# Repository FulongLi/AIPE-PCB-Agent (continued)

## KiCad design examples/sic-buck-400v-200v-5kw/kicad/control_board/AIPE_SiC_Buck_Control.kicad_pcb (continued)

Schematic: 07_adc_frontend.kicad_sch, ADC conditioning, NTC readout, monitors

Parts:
C63, C64: 1u/50V; C_0805_2012Metric
C65, C66, C67: 100n/50V; C_0603_1608Metric
C68, C69, C70, C71, C72, C73, C74, C75: 1n/50V; C_0603_1608Metric
J7: J_NTC: Vishay NTCALUG01A103F heatsink lug NTC (10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; PinHeader_1x02_P2.54mm_Vertical
R64: 2.2k; R_0603_1608Metric
R65: 32.4k; R_0603_1608Metric
R66: 10k; R_0603_1608Metric
R67, R68, R69, R70, R71, R72, R73, R74: 1k; R_0603_1608Metric
U15: REF3130AIDBZR; SOT-23
U16: LM61CIM3/NOPB; SOT-23

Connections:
3V3: C63.1, C67.1, U15.1 (IN), U16.1 (+VS); also elsewhere on the board
ADC_I12V: C73.1, R72.2; also elsewhere on the board
ADC_ISENSE: C69.1, R68.2; also elsewhere on the board
ADC_ISENSE_REF: C72.1, R71.2; also elsewhere on the board
ADC_TEMP_CTRL: C71.1, R70.2; also elsewhere on the board
ADC_TEMP_HS: C70.1, R69.2; also elsewhere on the board
ADC_V12V: C75.1, R74.2; also elsewhere on the board
ADC_VIN: C68.1, R67.2; also elsewhere on the board
ADC_VOUT: C74.1, R73.2; also elsewhere on the board
GND_CTRL: C63.2, C64.2, C65.2, C66.2, C67.2, C68.2, C69.2, C70.2, C71.2, C72.2, C73.2, C74.2, C75.2, J7.2, R66.2, U15.3 (GND), U16.3 (GND); also elsewhere on the board
I12V_MON: R72.1; also elsewhere on the board
ISENSE: R68.1; also elsewhere on the board
ISENSE_REF: R71.1; also elsewhere on the board
OTP_REF: C66.1, R65.2, R66.1; also elsewhere on the board
REF3V0: C64.1, R64.1, R65.1, U15.2 (OUT)
TEMP_CTRL: R70.1, U16.2 (VOUT)
TEMP_HS_NTC: C65.1, J7.1, R64.2, R69.1; also elsewhere on the board
V12V_MON: R74.1; also elsewhere on the board
VIN_SENSE: R67.1; also elsewhere on the board
VOUT_SENSE: R73.1; also elsewhere on the board

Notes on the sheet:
ADC conditioning, NTC readout, monitors
1 k + 1 nF at every ADC input; heatsink NTC with 2.2 k to REF3V0 (REF3130); OTP threshold 42.2 k / 10 k = 0.575 V (110 C); LM61.
REF3130, heatsink NTC, OTP threshold, LM61
ADC anti-alias RC networks

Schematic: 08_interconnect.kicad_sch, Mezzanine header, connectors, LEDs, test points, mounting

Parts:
D3, D6: LED red; LED_0805_2012Metric
D4, D5: LED green; LED_0805_2012Metric
H1, H2, H3, H4: M3; MountingHole_3.2mm_M3
J8: J_MEZZ: 2 x 25 header to the power-board SSW-125-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; PinHeader_2x25_P2.54mm_Vertical
R75: 10k; R_0603_1608Metric
R76: 4.7k; R_0603_1608Metric
R77, R78, R79: 1.5k; R_0603_1608Metric
TP1: 3V3; TestPoint_Pad_D2.0mm
TP2: 1V9; TestPoint_Pad_D2.0mm
TP3: 5V; TestPoint_Pad_D2.0mm
TP4: 12V_PROT; TestPoint_Pad_D2.0mm
TP5, TP6: GND_CTRL; TestPoint_Pad_D2.0mm
TP7: PWM_H; TestPoint_Pad_D2.0mm
TP8: PWM_L; TestPoint_Pad_D2.0mm
TP9: FAULT_N; TestPoint_Pad_D2.0mm
TP10: ARM; TestPoint_Pad_D2.0mm
TP11: FAULT_LATCH_N; TestPoint_Pad_D2.0mm
TP12: GATE_EN; TestPoint_Pad_D2.0mm
TP13: XRS_N; TestPoint_Pad_D2.0mm
TP14: VIN_SENSE; TestPoint_Pad_D2.0mm
TP15: VOUT_SENSE; TestPoint_Pad_D2.0mm
TP16: ISENSE; TestPoint_Pad_D2.0mm

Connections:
1V9: TP2.1; also elsewhere on the board
3V3: J8.39, J8.40, R75.1, TP1.1; also elsewhere on the board
5V: TP3.1; also elsewhere on the board
12V_PROT: J8.1, J8.2, J8.3, R76.1, TP4.1; also elsewhere on the board
ARM: TP10.1; also elsewhere on the board
BIAS_EN: J8.9; also elsewhere on the board
FAN_TACH: J8.29, R75.2; also elsewhere on the board
FAULT_LATCH_N: TP11.1; also elsewhere on the board
FAULT_N: J8.35, R77.1, TP9.1; also elsewhere on the board
FLT_H_N: J8.20; also elsewhere on the board
FLT_L_N: J8.21; also elsewhere on the board
GATE_EN: TP12.1; also elsewhere on the board
GND_CTRL: D3.1 (K), D4.1 (K), D5.1 (K), D6.1 (K), J8.4, J8.5, J8.6, J8.8, J8.10, J8.12, J8.13, J8.15, J8.16, J8.18, J8.19, J8.22, J8.25, J8.26, J8.28, J8.31, J8.34, J8.38, J8.41, J8.42, J8.44, J8.46, J8.48, J8.50, TP5.1, TP6.1; also elsewhere on the board
ISENSE: J8.43, TP16.1; also elsewhere on the board
ISENSE_REF: J8.45; also elsewhere on the board
LED_12V_A: D3.2 (A), R76.2
LED_ARMED_A: D4.2 (A), R77.2
LED_FAULT: R79.1; also elsewhere on the board
LED_FAULT_A: D6.2 (A), R79.2
LED_RUN: R78.1; also elsewhere on the board
LED_RUN_A: D5.2 (A), R78.2
OC_N: J8.27; also elsewhere on the board
PG_BIAS_H_N: J8.32; also elsewhere on the board
PG_BIAS_L_N: J8.33; also elsewhere on the board
PG_BIAS_S_N: J8.30; also elsewhere on the board
PWM_H: J8.14, TP7.1; also elsewhere on the board
PWM_L: J8.17, TP8.1; also elsewhere on the board
RDY_H: J8.23; also elsewhere on the board
RDY_L: J8.24; also elsewhere on the board
RELAY_ON: J8.7; also elsewhere on the board
RESET_N: J8.11; also elsewhere on the board
SPARE_D1: J8.36; also elsewhere on the board
SPARE_D2: J8.37; also elsewhere on the board
VIN_SENSE: J8.47, TP14.1; also elsewhere on the board
VOUT_SENSE: J8.49, TP15.1; also elsewhere on the board
XRS_N: TP13.1; also elsewhere on the board

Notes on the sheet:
Mezzanine header, connectors, LEDs, test points, mounting
Mezzanine header TSW-125-07-G-D (pin assignment per design_decisions.json), indicator LEDs, test pads, 4 x M3.
Mezzanine header to the power board
Indicator LEDs
Test points
Mechanical

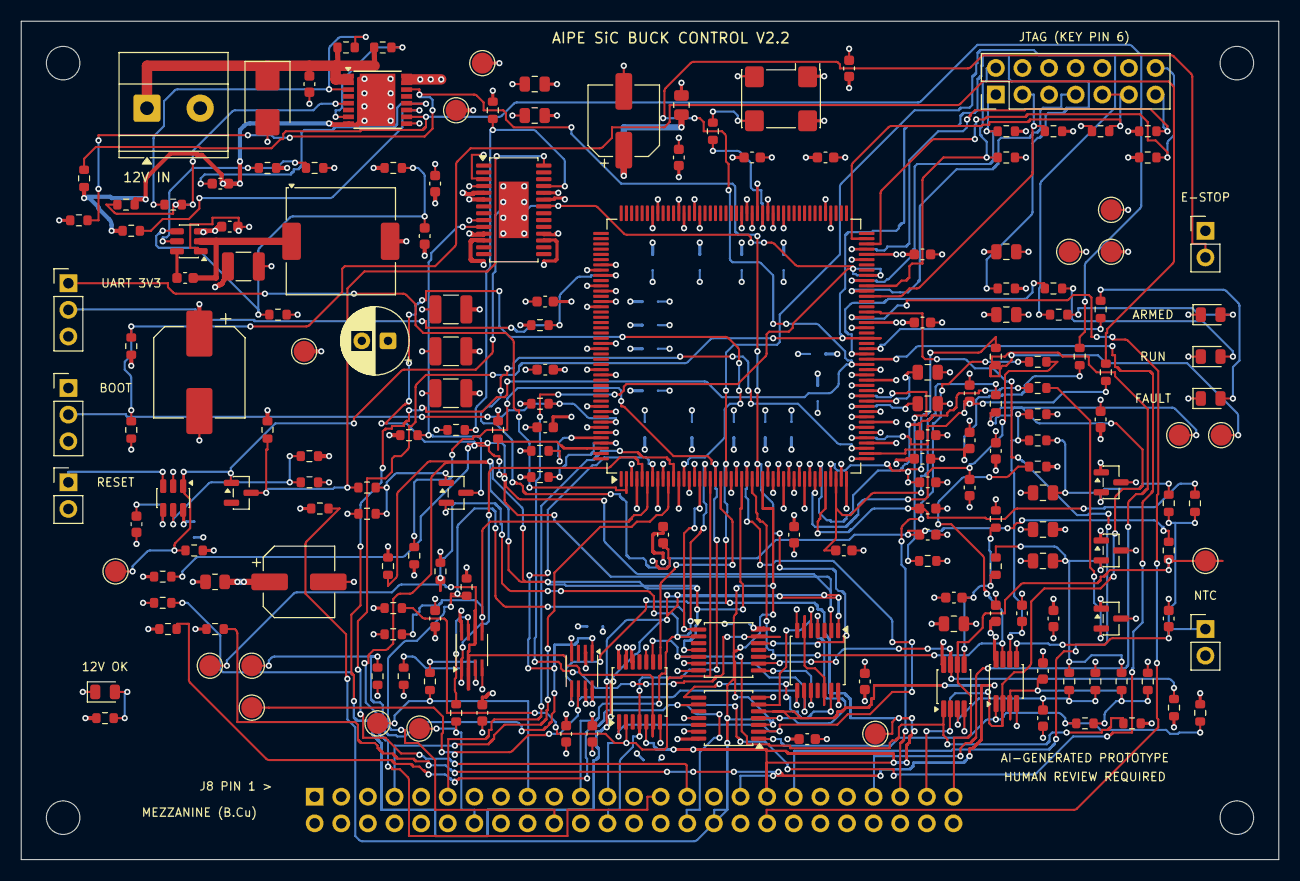
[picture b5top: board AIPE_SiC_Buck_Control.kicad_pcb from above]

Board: 4 copper layers, 120.0 x 80.0 mm, 211 parts (20 on the bottom side), 111 nets.

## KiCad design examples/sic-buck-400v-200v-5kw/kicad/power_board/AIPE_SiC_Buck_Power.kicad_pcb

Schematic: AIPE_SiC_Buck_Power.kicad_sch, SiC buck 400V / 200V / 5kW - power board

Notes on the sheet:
AI-GENERATED ENGINEERING PROTOTYPE - V2.2 - HUMAN REVIEW REQUIRED
Design basis: examples/sic-buck-400v-200v-5kw/design/design_decisions.json (schema 3, 2026-10-10) - single source of truth; electrical model automation/kicad_tools/sic_buck_power_model.py; generator automation/kicad_tools/generate_sic_schematics.py. 400 V (360-440 V) to 200 V / 25 A / 5 kW / 50 kHz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

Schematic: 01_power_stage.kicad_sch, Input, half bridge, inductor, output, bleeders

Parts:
C1, C2, C3, C4, C5, C6, C7, C8, C9, C10: 0.47u/630V; C_2220_5750Metric
C11, C12: 20uF/800V film; C_Film_41.5x28x37_P37.5x10.2
C13, C14: 60uF/450V film; C_Film_41.5x30x45_P37.5x20.3
C15: 1n/1kV; C_1812_4532Metric; not fitted
C16, C17: 0.47u/630V; C_2220_5750Metric; not fitted
C18, C19: 10n/300VAC; C_Disc_D12.5mm_W5.0mm_P10.00mm; not fitted
D1, D2: LED red; LED_0805_2012Metric
H1: PE M4 stud; MountingHole_4.3mm_M4_Pad
J1: VIN_RAW (+IN); Wuerth_REDCUBE-THR_WP-THRSH_74651195_THR
J2: PGND (-IN); Wuerth_REDCUBE-THR_WP-THRSH_74651195_THR
J3: VOUT (+OUT); Wuerth_REDCUBE-THR_WP-THRSH_74651195_THR
J4: PGND (-OUT); Wuerth_REDCUBE-THR_WP-THRSH_74651195_THR
J5: RLY_A (VIN_RAW); Wuerth_REDCUBE-THR_WP-THRSH_74651195_THR
J6: RLY_B (VIN); Wuerth_REDCUBE-THR_WP-THRSH_74651195_THR
L1: 272uH/25A toroid; L_Toroid_HF58x2_D69_H48_P25.4
Q1, Q2: C4MS025120K; TO-247-4_Vertical
R1, R2, R3: 120k; R_2512_6332Metric
R4, R5, R6: 150k; R_1206_3216Metric
R7, R8: 100k; R_2512_6332Metric
R9, R10: 100k; R_1206_3216Metric
R11: 10; R_2512_6332Metric; not fitted
R12, R13: 0.47; R_2512_6332Metric; not fitted
R14: 0; R_2512_6332Metric; not fitted
R15, R16: 1M; R_2512_6332Metric
RT1: PTC precharge (re-select); PTC_Disc_D20_P10_Envelope
RV1: S20K385 MOV; RV_Disc_D21.5mm_W5.4mm_P10mm; not fitted
U10: TMCS1133C2AQDVGR; TMCS1133_DVG0010A_HV_Slot

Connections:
3V3: U10.9 (VS), U10.10 (VS); also elsewhere on the board
BLD_IN_1: R1.2, R2.1
BLD_IN_2: R2.2, R3.1
BLD_OUT_1: R7.2, R8.1
DAMP_MID: C16.2, C17.2, R12.1, R13.1
GND_CTRL: U10.3 (GND), U10.4 (ALERT); also elsewhere on the board
G_H: Q1.4 (G); also elsewhere on the board
G_L: Q2.4 (G); also elsewhere on the board
IND_IN_1: R4.2, R5.1
IND_IN_2: R5.2, R6.1
IND_IN_3: D1.2 (A), R6.2
IND_OUT_1: R9.2, R10.1
IND_OUT_2: D2.2 (A), R10.2
ISENSE: U10.6 (VOUT); also elsewhere on the board
KS_H: Q1.3 (KS); also elsewhere on the board
KS_L: Q2.3 (KS); also elsewhere on the board
OC_N: U10.7 (OC); also elsewhere on the board
PE: C18.2, C19.2, H1.1, R14.2, R16.2
PE_REF_MID: R15.2, R16.1
PGND: C1.2, C2.2, C3.2, C4.2, C5.2, C6.2, C7.2, C8.2, C9.2, C10.2, C11.2, C12.2, C13.2, C14.2, C15.2, C19.1, D1.1 (K), D2.1 (K), J2.1, J4.1, Q2.2 (S), R3.2, R8.2, R12.2, R13.2, R14.1, R15.1, RV1.2; also elsewhere on the board
SNUB_MID: C15.1, R11.2
SW: L1.1, Q1.2 (S), Q2.1 (D), R11.1; also elsewhere on the board
VIN: C1.1, C2.1, C3.1, C4.1, C5.1, C6.1, C7.1, C8.1, C9.1, C10.1, C11.1, C12.1, C16.1, C17.1, C18.1, J6.1, Q1.1 (D), R1.1, R4.1, RT1.2, RV1.1; also elsewhere on the board
VIN_RAW: J1.1, J5.1, RT1.1
VOC_SET: U10.8 (VOC); also elsewhere on the board
VOUT: C13.1, C14.1, J3.1, R7.1, R9.1, U10.2 (IN-); also elsewhere on the board
VOUT_L: L1.2, U10.1 (IN+)

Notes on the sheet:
Input, half bridge, inductor, output, bleeders
Q1/Q2 pads 1 D, 2 S, 3 KS, 4 G follow the Wolfspeed PRD 05966 front-view lead order - ASSUMPTION, verify the footprint pad-1 side before fabrication. HV classes: VIN_RAW/VIN (HV_VIN), SW (HV_SW), VOUT_L/VOUT (HV_VOUT), PGND (HV_PGND) plus bleeder, indicator, ladder-tap, snubber and damping nodes. D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
Power terminals, precharge PTC, MOV
Half bridge, HF capacitor bank, DC-link capacitors
Output inductor, current sensor, output capacitors
Bleeders and LIVE indicators
Snubber and damping leg (DNP)
PE network
Supply provenance (PWR_FLAG)

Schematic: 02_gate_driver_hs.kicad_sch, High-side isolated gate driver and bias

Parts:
C20: 100p/50V; C_0603_1608Metric
C21: 470p/50V; C_0603_1608Metric; not fitted
C22, C23, C25, C36, C37, C39: 4.7u/25V; C_1206_3216Metric
C24, C26, C28, C33, C38: 100n/50V; C_0603_1608Metric
C27: 1u/50V; C_0805_2012Metric
C29: 680p/50V; C_0603_1608Metric
C30, C31, C32: 10u/25V; C_1210_3225Metric
C34, C35: 330p/50V; C_0603_1608Metric
D3: US1M 1000V; D_SMA
D4: BAT42W Schottky; D_SOD-123; not fitted
L2: 744226S; L_CommonMode_Wuerth_WE-SL2
R17: 100; R_0603_1608Metric
R18, R34: 10k; R_0603_1608Metric
R19: 10; R_1206_3216Metric
R20: 3.3; R_1206_3216Metric
R21: 0; R_0603_1608Metric
R22: 10k; R_0805_2012Metric
R23: 1; R_0603_1608Metric; not fitted
R24: 2.2k; R_1206_3216Metric
R25: 4.99k; R_0603_1608Metric
R26: 1k; R_0603_1608Metric
R27, R28: 4.7k; R_0603_1608Metric
R29: 107k; R_0603_1608Metric
R30, R32: 16.2k; R_0603_1608Metric
R31: 9.76k; R_0603_1608Metric
R33: 1k; R_0805_2012Metric
TP1: VGS_H; TestPoint_2Pads_Pitch2.54mm_Drill0.8mm
U1: UCC21710QDWRQ1; UCC21710_DW0016A_Slot
U2: UCC14141QDWNRQ1; UCC14141_DWN0036A_Slot

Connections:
3V3: C27.1, C28.1, R27.1, R28.1, R34.1, U1.15 (VCC); also elsewhere on the board
12V_BIAS_H: C30.1, C31.1, C32.1, C33.1, L2.4 (W1B), U2.6 (VIN), U2.7 (VIN)
12V_PROT: L2.1 (W1A); also elsewhere on the board
BIAS_EN_F: U2.4 (ENA); also elsewhere on the board
DESAT_H_A: D3.2 (A), R24.2, R25.1
DESAT_H_OC: C29.1, D4.1 (K), R25.2, R26.1, U1.2 (OC)
FLT_H_N: R28.2, U1.13 (FLT); also elsewhere on the board
GNDP_H: C30.2, C31.2, C32.2, C33.2, L2.3 (W2B), U2.1 (GNDP), U2.2 (GNDP), U2.5 (GNDP), U2.8 (GNDP), U2.9 (GNDP), U2.10 (GNDP), U2.11 (GNDP), U2.12 (GNDP), U2.13 (GNDP), U2.14 (GNDP), U2.15 (GNDP), U2.16 (GNDP), U2.17 (GNDP), U2.18 (GNDP)
GND_CTRL: C20.2, C27.2, C28.2, L2.2 (W2A), R18.2, U1.9 (GND); also elsewhere on the board
G_H: R19.2, R20.2, R21.2, R22.1, R23.1, TP1.1; also elsewhere on the board
HS_CLMP: R21.1, U1.7 (CLMPI)
HS_FB_VDD: C34.1, R29.2, R30.1, U2.34 (FBVDD)
HS_FB_VEE: C35.1, R31.2, R32.1, U2.33 (FBVEE)
HS_GK: C21.1, R23.2
HS_OUTH: R19.1, U1.4 (OUTH)
HS_OUTL: R20.1, U1.6 (OUTL)
HS_RLIM: R33.1, U2.32 (RLIM)
KS_H: C21.2, C22.2, C23.2, C24.2, C25.1, C26.1, C29.2, C39.1, D4.2 (A), R22.2, R26.2, R31.1, R33.2, TP1.2, U1.1 (AIN), U1.3 (COM); also elsewhere on the board
PG_BIAS_H_N: R34.2, U2.3 (PG); also elsewhere on the board
PWM_H: R17.1; also elsewhere on the board
PWM_H_F: C20.1, R17.2, R18.1, U1.10 (IN+); also elsewhere on the board
PWM_L_F: U1.11 (IN-); also elsewhere on the board
RDY_H: R27.2, U1.12 (RDY); also elsewhere on the board
RESET_N_F: U1.14 (RST/EN); also elsewhere on the board
VDD_H: C22.1, C23.1, C24.1, C36.1, C37.1, C38.1, R24.1, R29.1, U1.5 (VDD), U2.28 (VDD), U2.29 (VDD)
VEE_H: C25.2, C26.2, C34.2, C35.2, C36.2, C37.2, C38.2, C39.2, R30.2, R32.2, U1.8 (VEE), U2.19 (VEE), U2.20 (VEE), U2.21 (VEE), U2.22 (VEE), U2.23 (VEE), U2.24 (VEE), U2.25 (VEE), U2.26 (VEE), U2.27 (VEE), U2.30 (VEE), U2.31 (VEE), U2.35 (VEEA), U2.36 (VEE)
VIN: D3.1 (K); also elsewhere on the board

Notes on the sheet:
High-side isolated gate driver and bias
UCC21710 IN+ = PWM_H_F, IN- = PWM_L_F (hardware interlock KR-GD-009); AIN tied to COM (CR-01); APWM not connected. UCC14141 VDD-VEE 19.0 V (107 k / 16.2 k) and COM-VEE 4.0 V (9.76 k / 16.2 k) give +15 V / -4 V at the gate; RLIM 1 k is a placeholder (human review). Decoupling sits between the driver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
HS isolated gate driver (UCC21710-Q1): PWM input, gate network, status pull-ups, decoupling
HS DESAT protection network
HS isolated bias supply (UCC14141-Q1)
Supply provenance (PWR_FLAG)

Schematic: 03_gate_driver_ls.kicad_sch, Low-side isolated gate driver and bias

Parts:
C40: 100p/50V; C_0603_1608Metric
C41: 470p/50V; C_0603_1608Metric; not fitted
C42, C43, C45, C56, C57, C59: 4.7u/25V; C_1206_3216Metric
C44, C46, C48, C53, C58: 100n/50V; C_0603_1608Metric
C47: 1u/50V; C_0805_2012Metric
C49: 680p/50V; C_0603_1608Metric
C50, C51, C52: 10u/25V; C_1210_3225Metric
C54, C55: 330p/50V; C_0603_1608Metric
D5: US1M 1000V; D_SMA
D6: BAT42W Schottky; D_SOD-123; not fitted
L3: 744226S; L_CommonMode_Wuerth_WE-SL2
R35: 100; R_0603_1608Metric
R36, R52: 10k; R_0603_1608Metric
R37: 10; R_1206_3216Metric
R38: 3.3; R_1206_3216Metric
R39: 0; R_0603_1608Metric
R40: 10k; R_0805_2012Metric
R41: 1; R_0603_1608Metric; not fitted
R42: 2.2k; R_1206_3216Metric
R43: 4.99k; R_0603_1608Metric
R44: 1k; R_0603_1608Metric
R45, R46: 4.7k; R_0603_1608Metric
R47: 107k; R_0603_1608Metric
R48, R50: 16.2k; R_0603_1608Metric
R49: 9.76k; R_0603_1608Metric
R51: 1k; R_0805_2012Metric
TP2: VGS_L; TestPoint_2Pads_Pitch2.54mm_Drill0.8mm
U3: UCC21710QDWRQ1; UCC21710_DW0016A_Slot
U4: UCC14141QDWNRQ1; UCC14141_DWN0036A_Slot

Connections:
3V3: C47.1, C48.1, R45.1, R46.1, R52.1, U3.15 (VCC); also elsewhere on the board
12V_BIAS_L: C50.1, C51.1, C52.1, C53.1, L3.4 (W1B), U4.6 (VIN), U4.7 (VIN)
12V_PROT: L3.1 (W1A); also elsewhere on the board
BIAS_EN_F: U4.4 (ENA); also elsewhere on the board
DESAT_L_A: D5.2 (A), R42.2, R43.1
DESAT_L_OC: C49.1, D6.1 (K), R43.2, R44.1, U3.2 (OC)
FLT_L_N: R46.2, U3.13 (FLT); also elsewhere on the board
GNDP_L: C50.2, C51.2, C52.2, C53.2, L3.3 (W2B), U4.1 (GNDP), U4.2 (GNDP), U4.5 (GNDP), U4.8 (GNDP), U4.9 (GNDP), U4.10 (GNDP), U4.11 (GNDP), U4.12 (GNDP), U4.13 (GNDP), U4.14 (GNDP), U4.15 (GNDP), U4.16 (GNDP), U4.17 (GNDP), U4.18 (GNDP)
GND_CTRL: C40.2, C47.2, C48.2, L3.2 (W2A), R36.2, U3.9 (GND); also elsewhere on the board
G_L: R37.2, R38.2, R39.2, R40.1, R41.1, TP2.1; also elsewhere on the board
KS_L: C41.2, C42.2, C43.2, C44.2, C45.1, C46.1, C49.2, C59.1, D6.2 (A), R40.2, R44.2, R49.1, R51.2, TP2.2, U3.1 (AIN), U3.3 (COM); also elsewhere on the board
LS_CLMP: R39.1, U3.7 (CLMPI)
LS_FB_VDD: C54.1, R47.2, R48.1, U4.34 (FBVDD)
LS_FB_VEE: C55.1, R49.2, R50.1, U4.33 (FBVEE)
LS_GK: C41.1, R41.2
LS_OUTH: R37.1, U3.4 (OUTH)
LS_OUTL: R38.1, U3.6 (OUTL)
LS_RLIM: R51.1, U4.32 (RLIM)
PG_BIAS_L_N: R52.2, U4.3 (PG); also elsewhere on the board
PWM_H_F: U3.11 (IN-); also elsewhere on the board
PWM_L: R35.1; also elsewhere on the board
PWM_L_F: C40.1, R35.2, R36.1, U3.10 (IN+); also elsewhere on the board
RDY_L: R45.2, U3.12 (RDY); also elsewhere on the board
RESET_N_F: U3.14 (RST/EN); also elsewhere on the board
SW: D5.1 (K); also elsewhere on the board
VDD_L: C42.1, C43.1, C44.1, C56.1, C57.1, C58.1, R42.1, R47.1, U3.5 (VDD), U4.28 (VDD), U4.29 (VDD)
VEE_L: C45.2, C46.2, C54.2, C55.2, C56.2, C57.2, C58.2, C59.2, R48.2, R50.2, U3.8 (VEE), U4.19 (VEE), U4.20 (VEE), U4.21 (VEE), U4.22 (VEE), U4.23 (VEE), U4.24 (VEE), U4.25 (VEE), U4.26 (VEE), U4.27 (VEE), U4.30 (VEE), U4.31 (VEE), U4.35 (VEEA), U4.36 (VEE)

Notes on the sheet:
Low-side isolated gate driver and bias
Mirror of the high-side channel: IN+ = PWM_L_F, IN- = PWM_H_F; DESAT diode cathode on SW; KS_L is never joined to PGND on the PCB (KR-PCB-003). Isolation slot under the library SOIC-16W footprint is a layout task.
LS isolated gate driver (UCC21710-Q1): PWM input, gate network, status pull-ups, decoupling
LS DESAT protection network
LS isolated bias supply (UCC14141-Q1)
Supply provenance (PWR_FLAG)

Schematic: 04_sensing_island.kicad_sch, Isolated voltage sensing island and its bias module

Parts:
C60, C61, C62: 10u/25V; C_1210_3225Metric
C63, C68, C72, C73, C76, C77: 100n/50V; C_0603_1608Metric
C64, C65: 330p/50V; C_0603_1608Metric
C66, C67, C69: 4.7u/25V; C_1206_3216Metric
C70, C74: 1n/50V; C_0603_1608Metric
C71, C75: 100p/50V; C_0603_1608Metric
L4: 744226S; L_CommonMode_Wuerth_WE-SL2
R53: 80.6k; R_0603_1608Metric
R54, R55, R56: 16.2k; R_0603_1608Metric
R57: 160; R_1206_3216Metric
R58, R63, R66: 10k; R_0603_1608Metric
R59, R60, R61, R62, R64, R65: 750k; R_1206_3216Metric
U5: UCC14141QDWNRQ1; UCC14141_DWN0036A_Slot
U6, U7: AMC1311BDWVR; AMC1311_DWV0008A_Slot

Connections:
3V3: C73.1, C77.1, R58.1, U6.8 (VDD2), U7.8 (VDD2); also elsewhere on the board
5V_ISO: C69.1, C72.1, C76.1, R55.1, R57.2, U6.1 (VDD1), U7.1 (VDD1)
12V_BIAS_S: C60.1, C61.1, C62.1, C63.1, L4.4 (W1B), U5.6 (VIN), U5.7 (VIN)
12V_PROT: L4.1 (W1A); also elsewhere on the board
BIAS_EN_F: U5.4 (ENA); also elsewhere on the board
GNDP_S: C60.2, C61.2, C62.2, C63.2, L4.3 (W2B), U5.1 (GNDP), U5.2 (GNDP), U5.5 (GNDP), U5.8 (GNDP), U5.9 (GNDP), U5.10 (GNDP), U5.11 (GNDP), U5.12 (GNDP), U5.13 (GNDP), U5.14 (GNDP), U5.15 (GNDP), U5.16 (GNDP), U5.17 (GNDP), U5.18 (GNDP)
GND_CTRL: C73.2, C77.2, L4.2 (W2A), U6.5 (GND2), U7.5 (GND2); also elsewhere on the board
ISO_15V: C66.1, C67.1, C68.1, R53.1, U5.28 (VDD), U5.29 (VDD)
ISO_FB_VDD: C64.1, R53.2, R54.1, U5.34 (FBVDD)
ISO_FB_VEE: C65.1, R55.2, R56.1, U5.33 (FBVEE)
ISO_RLIM: R57.1, U5.32 (RLIM)
PGND: C64.2, C65.2, C66.2, C67.2, C68.2, C69.2, C70.2, C71.2, C72.2, C74.2, C75.2, C76.2, R54.2, R56.2, R63.2, R66.2, U5.19 (VEE), U5.20 (VEE), U5.21 (VEE), U5.22 (VEE), U5.23 (VEE), U5.24 (VEE), U5.25 (VEE), U5.26 (VEE), U5.27 (VEE), U5.30 (VEE), U5.31 (VEE), U5.35 (VEEA), U5.36 (VEE), U6.3 (SHTDN), U6.4 (GND1), U7.3 (SHTDN), U7.4 (GND1); also elsewhere on the board
PG_BIAS_S_N: R58.2, U5.3 (PG); also elsewhere on the board
VIN: R59.1; also elsewhere on the board
VIN_DIV: C70.1, C71.1, R62.2, R63.1, U6.2 (IN)
VIN_DIV_T1: R59.2, R60.1
VIN_DIV_T2: R60.2, R61.1
VIN_DIV_T3: R61.2, R62.1
VIN_OUTN: U6.6 (OUTN); also elsewhere on the board
VIN_OUTP: U6.7 (OUTP); also elsewhere on the board
VOUT: R64.1; also elsewhere on the board
VOUT_DIV: C74.1, C75.1, R65.2, R66.1, U7.2 (IN)
VOUT_DIV_T1: R64.2, R65.1
VOUT_OUTN: U7.6 (OUTN); also elsewhere on the board
VOUT_OUTP: U7.7 (OUTP); also elsewhere on the board

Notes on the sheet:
Isolated voltage sensing island and its bias module
Third UCC14141 (CR-12): VDD-VEE 15 V (80.6 k / 16.2 k, A-P2), COM-VEE 5.0 V = 5V_ISO, VEE = PGND. AMC1311 ladders 4 x 750 k (VIN, 602 V full scale) and 2 x 750 k (VOUT, 302 V) with 10.0 k bottoms; the taps VIN_DIV_T1..T3 and VOUT_DIV_T1 are HV nodes (classes HV_VIN / HV_VOUT, 120 V steps).
ISO isolated bias supply (UCC14141-Q1)
Isolated VIN / VOUT sensing (AMC1311)
Supply provenance (PWR_FLAG)

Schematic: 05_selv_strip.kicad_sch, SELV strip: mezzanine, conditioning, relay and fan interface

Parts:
C78, C79: 100p/50V; C_0603_1608Metric
C80, C86, C87, C89: 100n/50V; C_0603_1608Metric
C81, C82, C83, C84: 330p/50V; C_0603_1608Metric
C85, C88: 1u/50V; C_0805_2012Metric
C90: 100u/25V; CP_Elec_8x10.5
C91: 10u/25V; C_1210_3225Metric
D7: SS14 Schottky; D_SMA
J7: Mezzanine 2x25 socket; PinSocket_2x25_P2.54mm_Vertical
J8: FAN 12V/GND/TACH; PinHeader_1x03_P2.54mm_Vertical
J9: Relay coil K1; TerminalBlock_Phoenix_MKDS-1,5-2-5.08_1x02_P5.08mm_Horizont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
Q3: AO3400A; SOT-23
R67, R69, R85: 100; R_0603_1608Metric
R68, R70, R71, R73, R75, R77, R81, R84, R86: 10k; R_0603_1608Metric
R72, R74, R76, R78: 15k; R_0603_1608Metric
R79: 2.32k; R_0603_1608Metric
R80: 1k; R_0603_1608Metric
R82: 6.65k; R_0603_1608Metric
R83: 1.01k; R_0603_1608Metric
U8: OPA2320AIDGKR; VSSOP-8_3x3mm_P0.65mm
U9: REF3125AIDBZR; SOT-23

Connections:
3V3: C80.1, C85.1, C87.1, C88.1, J7.39, J7.40, R81.1, R84.1, U8.8 (V+), U9.1 (IN); also elsewhere on the board
12V_PROT: C90.1, C91.1, D7.1 (K), J7.1, J7.2, J7.3, J8.1, J9.1; also elsewhere on the board
BIAS_EN: J7.9, R69.1
BIAS_EN_F: C79.1, R69.2, R70.1; also elsewhere on the board
FAN_TACH: J7.29, J8.3, R84.2
FAULT_N: J7.35; also elsewhere on the board
FLT_H_N: J7.20; also elsewhere on the board
FLT_L_N: J7.21; also elsewhere on the board
GND_CTRL: C78.2, C79.2, C80.2, C81.2, C83.2, C85.2, C86.2, C87.2, C88.2, C89.2, C90.2, C91.2, J7.4, J7.5, J7.6, J7.8, J7.10, J7.12, J7.13, J7.15, J7.16, J7.18, J7.19, J7.22, J7.25, J7.26, J7.28, J7.31, J7.34, J7.38, J7.41, J7.42, J7.44, J7.46, J7.48, J7.50, J8.2, Q3.2 (S), R68.2, R70.2, R72.2, R76.2, R80.2, R83.2, R86.2, U8.4 (V-), U9.3 (GND); also elsewhere on the board
ISENSE: J7.43; also elsewhere on the board
ISENSE_REF: C89.1, J7.45, R82.2, R83.1
K1_LOW: D7.2 (A), J9.2, Q3.3 (D)
OC_N: J7.27, R81.2; also elsewhere on the board
PG_BIAS_H_N: J7.32; also elsewhere on the board
PG_BIAS_L_N: J7.33; also elsewhere on the board
PG_BIAS_S_N: J7.30; also elsewhere on the board
PWM_H: J7.14; also elsewhere on the board
PWM_L: J7.17; also elsewhere on the board
RDY_H: J7.23; also elsewhere on the board
RDY_L: J7.24; also elsewhere on the board
REF2V5_PB: C86.1, R79.1, R82.1, U9.2 (OUT)
RELAY_ON: J7.7, R85.1
RESET_N: J7.11, R67.1
RESET_N_F: C78.1, R67.2, R68.1; also elsewhere on the board
RLY_G: Q3.1 (G), R85.2, R86.1
SPARE_D1: J7.36; also elsewhere on the board
SPARE_D2: J7.37; also elsewhere on the board
VIN_AMP_N: C82.1, R73.2, R74.1, U8.2 (-INA)
VIN_AMP_P: C81.1, R71.2, R72.1, U8.3 (+INA)
VIN_OUTN: R73.1; also elsewhere on the board
VIN_OUTP: R71.1; also elsewhere on the board
VIN_SENSE: C82.2, J7.47, R74.2, U8.1 (OUTA); also elsewhere on the board
VOC_SET: R79.2, R80.1; also elsewhere on the board
VOUT_AMP_N: C84.1, R77.2, R78.1, U8.6 (-INB)
VOUT_AMP_P: C83.1, R75.2, R76.1, U8.5 (+INB)
VOUT_OUTN: R77.1; also elsewhere on the board
VOUT_OUTP: R75.1; also elsewhere on the board
VOUT_SENSE: C84.2, J7.49, R78.2, U8.7 (OUTB); also elsewhere on the board

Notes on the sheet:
SELV strip: mezzanine, conditioning, relay and fan interface
Mezzanine socket SSW-125-01-G-D with the pin assignment of design_decisions.json; receiving networks 100 ohm / 100 pF / 10 k pull-down on RESET_N and BIAS_EN (A-P6); OPA2320 difference amplifiers gain 1.5; REF3125 -> VOC_SET 0.750 V (I_OC 37.5 A); ISENSE_REF = 0.1 x 3V3 (A-P1); AO3400A + SS14 relay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
Mezzanine socket and receiving networks
OPA2320 difference amplifiers
REF3125 reference, OC threshold, ISENSE_REF
Relay coil drive, fan header, 12 V bulk
Supply provenance (PWR_FLAG)

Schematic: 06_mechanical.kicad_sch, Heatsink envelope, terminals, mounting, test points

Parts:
H2, H3, H4, H5, H6, H7: M4 standoff; MountingHole_4.3mm_M4
H8, H9, H10, H11: M3 standoff; MountingHole_3.2mm_M3
HS1: LAM 5 D K 100 12; HS_LAM5DK_100x100_H50
TP3: 3V3; TestPoint_Pad_D2.0mm
TP4, TP5: GND_CTRL; TestPoint_Pad_D2.0mm
TP6: PWM_H_F; TestPoint_Pad_D2.0mm
TP7: PWM_L_F; TestPoint_Pad_D2.0mm
TP8: FAULT_N; TestPoint_Pad_D2.0mm
TP9: ISENSE; TestPoint_Pad_D2.0mm
TP10: VIN_SENSE; TestPoint_Pad_D2.0mm
TP11: VOUT_SENSE; TestPoint_Pad_D2.0mm
TP12: SPARE_D1; TestPoint_Pad_D2.0mm
TP13: SPARE_D2; TestPoint_Pad_D2.0mm

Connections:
3V3: TP3.1; also elsewhere on the board
FAULT_N: TP8.1; also elsewhere on the board
GND_CTRL: TP4.1, TP5.1; also elsewhere on the board
ISENSE: TP9.1; also elsewhere on the board
PWM_H_F: TP6.1; also elsewhere on the board
PWM_L_F: TP7.1; also elsewhere on the board
SPARE_D1: TP12.1; also elsewhere on the board
SPARE_D2: TP13.1; also elsewhere on the board
VIN_SENSE: TP10.1; also elsewhere on the board
VOUT_SENSE: TP11.1; also elsewhere on the board

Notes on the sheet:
Heatsink envelope, terminals, mounting, test points
Heatsink envelope LAM 5 D K 100 12 (corner holes are placeholders), 6 x M4 baseplate standoffs, 4 x M3 control-board standoffs, bare-PCB test pads. The PE stud and PGND- PE network are on sheet 01.
Heatsink envelope and mounting holes
Bare-PCB test pads (SELV signals)

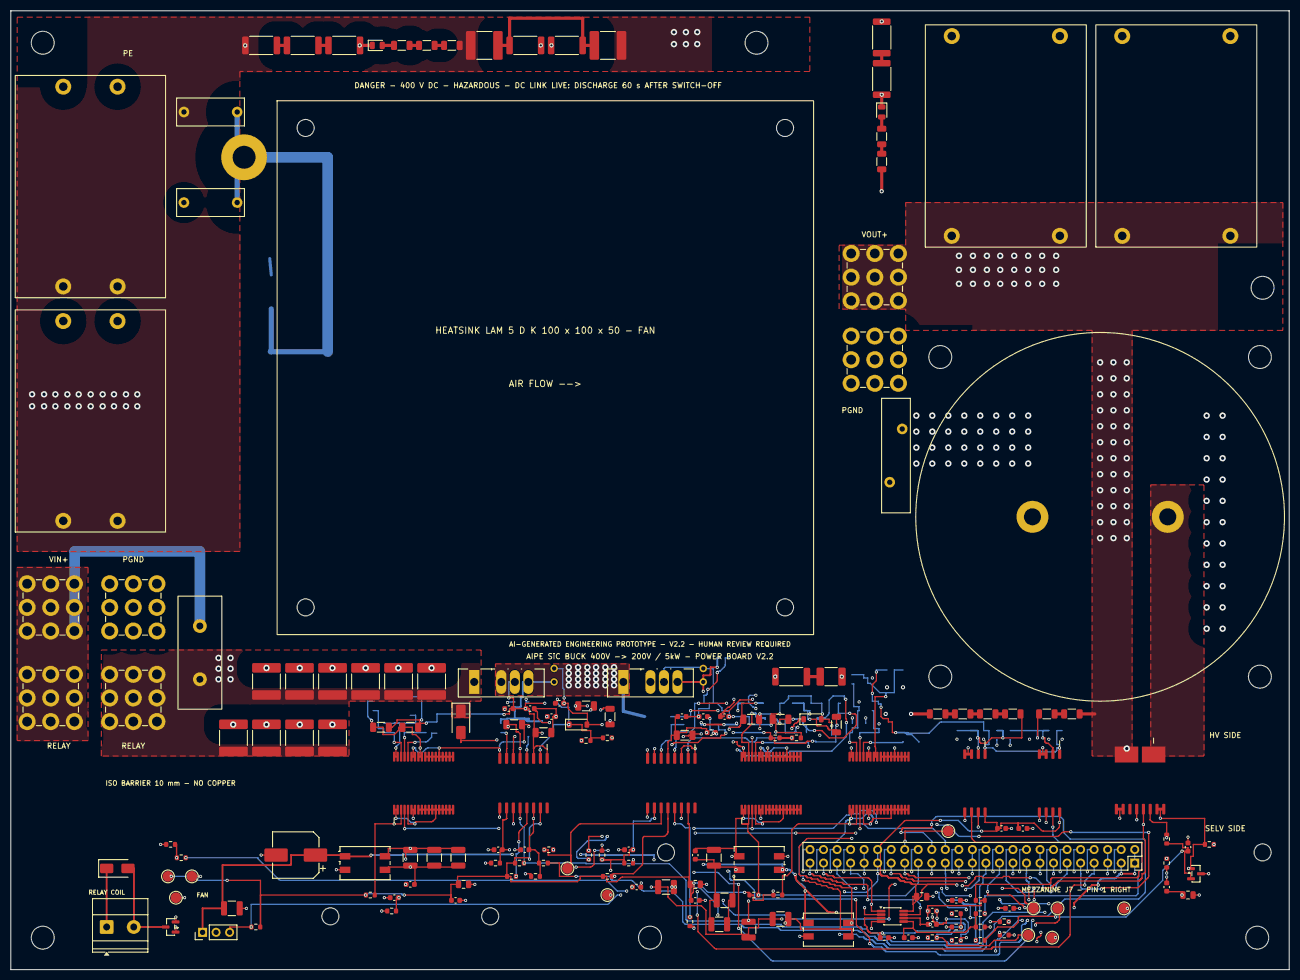
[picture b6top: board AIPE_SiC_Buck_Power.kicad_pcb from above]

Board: 4 copper layers, 240.0 x 180.0 mm, 237 parts (55 on the bottom side), 101 nets.

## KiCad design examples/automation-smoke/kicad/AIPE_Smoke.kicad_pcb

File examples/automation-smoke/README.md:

# KiCad automation smoke test

This is a passive 10k/10k divider with a three-pin connector. It is not the
1 kW converter. Sources, reports and outputs demonstrate the CAD pipeline only.

The 25 x 18 mm, two-layer board has three components, three nets, routed top and
bottom tracks, a through via and a filled bottom ground zone. All symbol pins
are connected. Official KiCad symbols and footprints are retained locally as
small library subsets. KiCad's installed 3D library supplies the component models.

## Run

1. Configure the existing KiCad CLI/Python in `.aipe/local-tools.json`.
2. Run `automation/kicad_tools/generate_smoke.py` using KiCad's bundled Python.
3. Run `python -m automation.kicad_tools.run_check erc examples/automation-smoke/kicad/AIPE_Smoke.kicad_sch --output examples/automation-smoke/verification`.
4. Run the same wrapper with `drc` and the `.kicad_pcb` source.
5. Run `python -m automation.kicad_tools.export_outputs examples/automation-smoke/kicad/AIPE_Smoke.kicad_pro --output <fresh-output-directory>`.

The checked-in successful exports are under `outputs/`. Export deliberately
requires a fresh directory so stale files cannot establish a passing run.
`python -m automation.verification.verify_smoke` checks the latest reports,
source hashes, exact three-net connectivity and the recorded export hashes.

## Observed result

KiCad 10.0.7 on Windows: ERC zero findings; DRC zero findings, unconnected items
and schematic-parity issues. No checks were disabled by the generator. The
reports list KiCad's default ignored checks explicitly; no exclusions were added.
Schematic PDF, four-page layer PDF, Gerber, drill, BOM, positions, STEP and
front/back/isometric images exported successfully. The final schematic and four
PCB PDF pages were rendered and visually inspected. STEP includes component
models, confirmed by the board renders. The exported netlist matches all seven
expected component-pin connections exactly.

Early failed runs remain in `verification/` as diagnostic history. The
`smoke-result.json` identifies the passing evidence. This test establishes only
this small pipeline, not the correctness of future converter circuitry or layout.

For non-Windows installations provide `AIPE_KICAD_DATA` if the data directory is
not beside the executable at `../share/kicad`, and use an interpreter that can
import the installed KiCad PCB bindings. Those hosts are not tested yet.

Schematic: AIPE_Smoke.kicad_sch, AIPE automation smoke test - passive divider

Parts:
J1: VIN_VOUT_GND; PinHeader_1x03_P2.54mm_Vertical
R1, R2: 10k; R_0805_2012Metric

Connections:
/GND: J1.3, R2.2
/VIN: J1.1, R1.1
/VOUT: J1.2, R1.2, R2.1

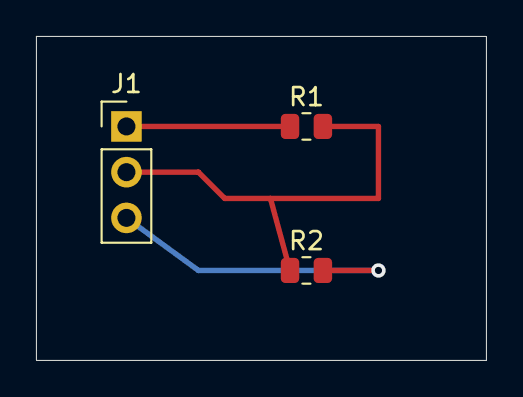
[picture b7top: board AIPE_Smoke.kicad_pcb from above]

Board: 2 copper layers, 25.0 x 18.0 mm, 3 parts (0 on the bottom side), 3 nets.

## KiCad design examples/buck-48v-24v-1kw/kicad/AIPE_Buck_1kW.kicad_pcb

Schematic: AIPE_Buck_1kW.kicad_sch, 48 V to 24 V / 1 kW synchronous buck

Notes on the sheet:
AI-GENERATED ENGINEERING PROTOTYPE - V1 - HUMAN REVIEW REQUIRED
Design basis: 36-54 V input / 24 V 41.67 A / 100 kHz / 150 MHz F28335 Hardware review prototype. Firmware control loop and thermal performance are unvalidated. All inter-page connections use explicit global net labels. GND is one continuous electrical net.

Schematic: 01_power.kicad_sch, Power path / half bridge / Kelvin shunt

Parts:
C15, C16, C17, C18, C19, C20, C21, C22: 2.2u/100V; C_1210_3225Metric
D1: SMCJ54A; D_SMC
F1: 40A/70V; MIDI_70V_M6_P30
J1: VIN+; Wuerth_REDCUBE-THR_WP-THRSH_74651195_THR
J2: VIN-; Wuerth_REDCUBE-THR_WP-THRSH_74651195_THR
J3: VOUT+; Wuerth_REDCUBE-THR_WP-THRSH_74651195_THR
J4: VOUT-; Wuerth_REDCUBE-THR_WP-THRSH_74651195_THR
L1: 10uH/83A; IHXL2000VZ_10uH_Upright
Q1, Q2, Q3, Q4: CSD19536KCS; TO-220-3_Vertical
R9: 2m/6W/Kelvin; CSS4J_4026_Kelvin

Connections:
GH1: Q1.1 (G); also elsewhere on the board
GH2: Q2.1 (G); also elsewhere on the board
GL1: Q3.1 (G); also elsewhere on the board
GL2: Q4.1 (G); also elsewhere on the board
GND: C15.2, C16.2, C17.2, C18.2, C19.2, C20.2, C21.2, C22.2, D1.2 (A), J2.1, J4.1, Q3.3 (S), Q4.3 (S); also elsewhere on the board
IL_FORCE: L1.2, R9.1
ISENSE_N: R9.4; also elsewhere on the board
ISENSE_P: R9.3; also elsewhere on the board
SW: L1.1, Q1.3 (S), Q2.3 (S), Q3.2 (D), Q4.2 (D); also elsewhere on the board
VIN: C15.1, C16.1, C17.1, C18.1, C19.1, C20.1, C21.1, C22.1, D1.1 (K), F1.2, Q1.2 (D), Q2.2 (D); also elsewhere on the board
VIN_RAW: F1.1, J1.1
VOUT: J3.1, R9.2; also elsewhere on the board

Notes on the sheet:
Power path / half bridge / Kelvin shunt

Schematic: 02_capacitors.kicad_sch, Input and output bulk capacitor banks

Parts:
C1, C2, C3, C4, C5, C6, C7, C8, C9, C10, C11, C12, C13, C14: 470u/100V; CP_Radial_D18.0mm_P7.50mm
C23, C24, C25, C26: 1000u/50V; CP_Radial_D16.0mm_P7.50mm
R10: 10k; R_2512_6332Metric
R11: 2.4k; R_2512_6332Metric

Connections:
GND: C1.2, C2.2, C3.2, C4.2, C5.2, C6.2, C7.2, C8.2, C9.2, C10.2, C11.2, C12.2, C13.2, C14.2, C23.2, C24.2, C25.2, C26.2, R10.2, R11.2; also elsewhere on the board
VIN: C1.1, C2.1, C3.1, C4.1, C5.1, C6.1, C7.1, C8.1, C9.1, C10.1, C11.1, C12.1, C13.1, C14.1, R10.1; also elsewhere on the board
VOUT: C23.1, C24.1, C25.1, C26.1, R11.1; also elsewhere on the board

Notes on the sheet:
Input and output bulk capacitor banks

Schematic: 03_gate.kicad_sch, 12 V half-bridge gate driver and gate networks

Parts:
C27, C28: 22u/25V; C_1210_3225Metric
C29: 2.2u/25V; C_0805_2012Metric
C30, C31: 100n/50V; C_0805_2012Metric
R1, R3, R5, R7: 4.7; R_0805_2012Metric
R2, R4, R6, R8, R12, R13: 10k; R_0805_2012Metric
U1: UCC27211DDAR; SOIC-8-1EP_3.9x4.9mm_P1.27mm_EP2.95x4.9mm_Mask2.71x3.4mm

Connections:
AUX12: C27.1, C28.1, C31.1, U1.1 (VDD); also elsewhere on the board
BOOT: C29.1, C30.1, U1.2 (HB)
GH1: R1.2, R2.1; also elsewhere on the board
GH2: R3.2, R4.1; also elsewhere on the board
GL1: R5.2, R6.1; also elsewhere on the board
GL2: R7.2, R8.1; also elsewhere on the board
GND: C27.2, C28.2, C31.2, R6.2, R8.2, R12.2, R13.2, U1.7 (VSS), U1.9 (EP); also elsewhere on the board
HI: R12.1, U1.5 (HI); also elsewhere on the board
HO: R1.1, R3.1, U1.3 (HO)
LI: R13.1, U1.6 (LI); also elsewhere on the board
LO: R5.1, R7.1, U1.8 (LO)
SW: C29.2, C30.2, R2.2, R4.2, U1.4 (HS); also elsewhere on the board

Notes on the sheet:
12 V half-bridge gate driver and gate networks

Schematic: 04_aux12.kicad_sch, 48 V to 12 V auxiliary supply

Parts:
C32, C33: 2.2u/100V; C_1210_3225Metric
C34: 2.2n/50V; C_0805_2012Metric
C35, C36: 22u/25V; C_1210_3225Metric
C37: 3.3n/50V; C_0805_2012Metric
C38: 56p/50V; C_0805_2012Metric
L2: 68uH; L_Coilcraft_MSS1246T-XXX
R14: 100k; R_0805_2012Metric
R15, R17: 453k; R_0805_2012Metric
R16: 49.9k; R_0805_2012Metric
R18: 10k; R_0805_2012Metric
U2: LM5164DDAR; SOIC-8-1EP_3.9x4.9mm_P1.27mm_EP2.95x4.9mm_Mask2.71x3.4mm

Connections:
3V3: R18.1; also elsewhere on the board
AUX12: C35.1, C36.1, C37.2, L2.2, R15.1; also elsewhere on the board
BST12: C34.1, U2.7 (BST)
FB12: C38.2, R15.2, R16.1, U2.5 (FB)
GND: C32.2, C33.2, C35.2, C36.2, R14.2, R16.2, U2.1 (GND), U2.9 (EP); also elsewhere on the board
PG12_N: R18.2, U2.6 (PGOOD); also elsewhere on the board
RIPPLE12: C37.1, C38.1, R17.2
RON12: R14.1, U2.4 (RON)
SW12: C34.2, L2.1, R17.1, U2.8 (SW)
VIN: C32.1, C33.1, U2.2 (VIN), U2.3 (EN); also elsewhere on the board

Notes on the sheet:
48 V to 12 V auxiliary supply

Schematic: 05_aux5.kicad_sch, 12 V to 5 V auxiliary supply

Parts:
C39, C41: 100n/50V; C_0805_2012Metric
C40, C42, C43: 22u/25V; C_1210_3225Metric
C44: 56p/50V; C_0805_2012Metric
C45: 220u/16V; CP_Radial_D6.3mm_P2.50mm
L3: 10uH; L_Coilcraft_MSS1048-XXX
R19, R21: 100k; R_0805_2012Metric
R20: 20k; R_0805_2012Metric
R22: 13.3k; R_0805_2012Metric
U3: TPS54302DDCR; SOT-23-6

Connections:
5V: C42.1, C43.1, C44.1, C45.1, L3.2, R21.1; also elsewhere on the board
AUX12: C40.1, C41.1, R19.1, U3.3 (VIN); also elsewhere on the board
BST5: C39.1, U3.6 (BOOT)
EN5: R19.2, R20.1, U3.5 (EN)
FB5: C44.2, R21.2, R22.1, U3.4 (FB)
GND: C40.2, C41.2, C42.2, C43.2, C45.2, R20.2, R22.2, U3.1 (GND); also elsewhere on the board
SW5: C39.2, L3.1, U3.2 (SW)

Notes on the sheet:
12 V to 5 V auxiliary supply

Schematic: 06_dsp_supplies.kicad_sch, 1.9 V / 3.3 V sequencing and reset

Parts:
C46, C47: 100u/6.3V; CP_Elec_6.3x5.8
C48, C51: 100n/50V; C_0805_2012Metric
C49: 22u/25V; C_1210_3225Metric
C50: 10n/50V; C_0805_2012Metric
D2: BAT54; SOT-23
J5: RESET; PinHeader_1x02_P2.54mm_Vertical
Q5: MMBT3904; SOT-23
R23: 18.2k; R_0805_2012Metric
R24: 30.1k; R_0805_2012Metric
R25, R26, R27, R32, R33: 10k; R_0805_2012Metric
R28: 100k; R_0805_2012Metric
R29, R30: 0.1; R_0805_2012Metric
R31: 105k; R_0805_2012Metric
U4: TPS767D301PWPR; HTSSOP-28-1EP_4.4x9.7mm_P0.65mm_EP2.85x5.4mm
U5: TPS3808G01DBVR; SOT-23-6

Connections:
1V9: R23.1, R29.1, U4.23 (OUT1), U4.24 (OUT1); also elsewhere on the board
1V9_BULK: C46.1, R29.2
3V3: C51.1, R30.1, R33.1, U4.17 (OUT2), U4.18 (OUT2), U5.3 (MR_N), U5.6 (VDD); also elsewhere on the board
3V3_BULK: C47.1, R30.2
5V: C48.1, C49.1, R25.1, R26.1, R31.1, U4.5 (IN1), U4.6 (IN1), U4.11 (IN2), U4.12 (IN2); also elsewhere on the board
CORE_OK: D2.3 (K), R25.2, R27.1, U4.28 (RESET1_N)
FB19: R23.2, R24.1, U4.25 (FB1)
GND: C46.2, C47.2, C48.2, C49.2, C50.2, C51.2, J5.2, Q5.2 (E), R24.2, R28.2, R32.2, U4.3 (GND1), U4.4 (EN1_N), U4.9 (GND2), U4.29 (EP), U5.2 (GND); also elsewhere on the board
IO_EN_N: Q5.3 (C), R26.2, U4.10 (EN2_N)
MON5: R31.2, R32.1, U5.5 (SENSE)
RESET_CT: C50.1, U5.4 (CT)
SEQ_BASE: Q5.1 (B), R27.2, R28.1
XRS_N: D2.1 (A), J5.1, R33.2, U4.22 (RESET2_N), U5.1 (RESET_N); also elsewhere on the board

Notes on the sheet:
1.9 V / 3.3 V sequencing and reset

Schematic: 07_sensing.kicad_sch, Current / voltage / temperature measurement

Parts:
C52, C54, C55, C58, C59, C60, C61: 1n/50V; C_0805_2012Metric
C53, C56, C57: 100n/50V; C_0805_2012Metric
D3, D4, D5, D6, D7, D8, D9, D10: BAT54; SOT-23
R34, R35: 10; R_0805_2012Metric
R36: 121k; R_0805_2012Metric
R37, R39: 4.99k; R_0805_2012Metric
R38: 49.9k; R_0805_2012Metric
R40, R41, R42, R43: 100; R_0805_2012Metric
U6: INA240A1DR; SOIC-8_3.9x4.9mm_P1.27mm
U7: LM61CIM3/NOPB; SOT-23
U8: TLV9004IDR; SOIC-14_3.9x8.7mm_P1.27mm

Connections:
3V3: C53.1, C56.1, C57.1, D3.3 (K), D5.3 (K), D7.3 (K), D9.3 (K), U6.6 (VS), U7.1 (VS), U8.4 (V+); also elsewhere on the board
ADC_CURRENT: C60.1, D7.1 (A), D8.3 (K), R42.2; also elsewhere on the board
ADC_TEMP: C61.1, D9.1 (A), D10.3 (K), R43.2; also elsewhere on the board
ADC_VIN: C58.1, D3.1 (A), D4.3 (K), R40.2; also elsewhere on the board
ADC_VOUT: C59.1, D5.1 (A), D6.3 (K), R41.2; also elsewhere on the board
CURRENT_BUF: R42.1, U8.8 (OUT3), U8.9 (IN3-)
CURRENT_RAW: U6.5 (OUT), U8.10 (IN3+); also elsewhere on the board
GND: C53.2, C54.2, C55.2, C56.2, C57.2, C58.2, C59.2, C60.2, C61.2, D4.1 (A), D6.1 (A), D8.1 (A), D10.1 (A), R37.2, R39.2, U6.2 (GND), U6.3 (REF2), U6.7 (REF1), U7.3 (GND), U8.11 (V-); also elsewhere on the board
ISENSE_N: R35.1; also elsewhere on the board
ISENSE_N_F: C52.2, R35.2, U6.1 (IN-)
ISENSE_P: R34.1; also elsewhere on the board
ISENSE_P_F: C52.1, R34.2, U6.8 (IN+)
TEMP_BUF: R43.1, U8.13 (IN4-), U8.14 (OUT4)
TEMP_RAW: U7.2 (OUT), U8.12 (IN4+); also elsewhere on the board
VIN: R36.1; also elsewhere on the board
VIN_BUF: R40.1, U8.1 (OUT1), U8.2 (IN1-)
VIN_DIV: C54.1, R36.2, R37.1, U8.3 (IN1+); also elsewhere on the board
VOUT: R38.1; also elsewhere on the board
VOUT_BUF: R41.1, U8.6 (IN2-), U8.7 (OUT2)
VOUT_DIV: C55.1, R38.2, R39.1, U8.5 (IN2+); also elsewhere on the board

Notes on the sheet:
Current / voltage / temperature measurement

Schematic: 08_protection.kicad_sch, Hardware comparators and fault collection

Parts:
C62, C64, C65, C66, C67, C68: 100n/50V; C_0805_2012Metric
C63: 2.2u/25V; C_0805_2012Metric
D11, D12: BAT54; SOT-23
J6: STOP / external open-drain fault; PinHeader_1x02_P2.54mm_Vertical
R44: 1k; R_0805_2012Metric
R45: 24k; R_0805_2012Metric
R46: 10k; R_0805_2012Metric
R47: 15k; R_0805_2012Metric
R48: 51k; R_0805_2012Metric
R49: 62k; R_0805_2012Metric
R50: 4.7k; R_0805_2012Metric
U9: REF3125AIDBZR; SOT-23
U10, U11: LM2903BDR; SOIC-8_3.9x4.9mm_P1.27mm

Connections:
3V3: C62.1, R50.1, U9.1 (IN); also elsewhere on the board
5V: C67.1, C68.1, U10.8 (VCC), U11.8 (VCC); also elsewhere on the board
CURRENT_RAW: U10.2 (IN1-); also elsewhere on the board
FAULT_N: D11.1 (A), D12.1 (A), J6.1, R50.2, U10.1 (OUT1), U10.7 (OUT2), U11.1 (OUT1), U11.7 (OUT2); also elsewhere on the board
GND: C62.2, C63.2, C64.2, C65.2, C66.2, C67.2, C68.2, J6.2, R45.2, R47.2, R49.2, U9.3 (GND), U10.4 (GND), U11.4 (GND); also elsewhere on the board
OCP_REF: C64.1, R44.2, R45.1, U10.3 (IN1+)
OTP_REF: C65.1, R46.2, R47.1, U11.3 (IN1+)
PG12_N: D12.3 (K); also elsewhere on the board
REF2V5: C63.1, R44.1, R46.1, R48.1, U9.2 (OUT), U10.5 (IN2+)
TEMP_RAW: U11.2 (IN1-); also elsewhere on the board
UVLO_REF: C66.1, R48.2, R49.1, U11.6 (IN2-)
VIN_DIV: U11.5 (IN2+); also elsewhere on the board
VOUT_DIV: U10.6 (IN2-); also elsewhere on the board
XRS_N: D11.3 (K); also elsewhere on the board

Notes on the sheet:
Hardware comparators and fault collection
